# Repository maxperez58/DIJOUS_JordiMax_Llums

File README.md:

View this project on [CADLAB.io](https://cadlab.io/project/28977). 

DIJOUS_JordiMax_Llums

## Autors
- Max Pérez (@maxperez58)
- Jordi Godàs (@Jordi_Godas)

## Versió - v1.0 ## Curs - Assignatura de Disseny de PCBs amb KiCad - [Curs 2024-2025]

## Objectiu Descripció breu de l'objectiu del projecte.

L'objectiu d'aquest projecte és la realització d'un sistema de control per els diferents tipus de llums d'un vehícle automòvil. A més a més, s'ha incorporat un motor per al control de l'escombreta neteja-fars.

## Requisits i especificacions
- Llums curtes.
- Llums d'encreuament.
- Llums de circulacio dïurna.
- Intermitents.
- Motor escombreta neteja-fars.
- Sensor digital de llum, per activar les llums.

## Diagrama de blocs (Afegiu una imatge del diagrama de blocs)

_Figura 1.1: Diagrama de Blocs del nostre projecte_

## Taula de components
| Descripció | Manufacturer Number | Package | Datasheet | Proveïdor | Unitats |
|------------|--------------------|---------|----------|----------|---------|
| LDO-5V | REG1117-5 |SMD| [LT1117-5](https://www.mouser.es/datasheet/2/609/1117fd-2953685.pdf)| Mouser | 1 |
| LDO-3.3V | ADP7112ACBZ-3.3-R7 |SMD| [ADP7112ACBZ-3.3-R7 ](https://www.mouser.es/datasheet/2/609/ADP7112-3121706.pdf)| Mouser | 1 |
| Sensor de llum | BH1750FVI-TR |SMD| [BH1750FVI-TR](https://www.mouser.com/catalog/specsheets/Rohm_11162017_ROHMS34826-1.pdf)| Mouser | 1 |
| Relé | G5LE-1 DC12 |TO-220| [G5LE-1 DC12](https://www.mouser.es/datasheet/2/307/en_g5le-3447037.pdf)| Mouser | 2 |
| Buck converter | LM2596T-ADJ |SMD| [LM2596T-ADJ](https://www.ti.com/lit/ds/symlink/lm2596.pdf)| Texas Instruments | 1 |
| Transciever| MCP2551-I-SN |SMD| [MCP2551-I-SN](https://ww1.microchip.com/downloads/en/devicedoc/21667d.pdf) | Texas Instruments | 1 |
| Microcontrolador | PIC18F2580-I/SO |SMD| [PIC18F2580-I/SO](https://www.mouser.es/datasheet/2/268/39637d-3443674.pdf) | Mouser | 1 |
| Transistor NMOS | Si7336ADP |SMD| [Si7336ADP](https://www.vishay.com/docs/73152/si7336adp.pdf)| Mouser | 4 |
| Transistor BJT | ZXTN19020DFFTA |SMD| [ZXTN19020DFFTA](https://www.diodes.com/assets/Datasheets/ZXTN19020DFF.pdf) | Mouser | 5 |
| Traductor (3.3V-5V) | PCA9306D |SMD|[PCA9306D](https://www.ti.com/lit/ds/symlink/pca9306.pdf?ts=1743021004009&ref_url=https%253A%252F%252Fwww.ti.com%252Fproduct%252FPCA9306) | Mouser | 1 |
| Sensor hall | TMAG5124G1CEDBZRQ1 |SMD| [TMAG5124G1CEDBZRQ1](https://www.ti.com/lit/ds/symlink/tmag5124-q1.pdf?ts=1743694512003&ref_url=https%253A%252F%252Fwww.mouser.es%252F) | Mouser | 1 |
| OPAMP's | LT6202CS5 |SMD| [LT6202CS5](https://www.mouser.es/datasheet/2/609/620234fd-2955338.pdf) | Mouser | 1 |
| Voltage Regulator | TLV1117-33 |SMD| [TLV1117-33](http://www.ti.com/lit/ds/symlink/tlv1117.pdf) | Mouser | 1 |
| Cristall | XT9M20ANA8M |SMD| [XT9M20ANA8M](https://datasheet.octopart.com/XT9M20ANA8M-Vishay-datasheet-41303490.pdf) | Mouser | 1 |
| Inductance | Ms 42 / 47 µH |SMD| [Ms 42 / 47 µH](https://neosid.de/import-data/product-pdf/neoFestind_Ms42.pdf) | Mouser | 1 |
| Diode | 1N4002 |THT| [1N4002](https://diotec.com/request/datasheet/1n4001.pdf) | Mouser | 1 |
| Diode | 1N5817 |THT| [1N5817](http://www.vishay.com/docs/88525/1n5817.pdf) | Mouser | 4 |
| LED | APTR3216PGW |SMD| [APTR3216PGW](https://www.mouser.es/datasheet/2/216/kingbright_kngbd00006-5-1736195.pdf) | Mouser | 2 |
| Zener diode | BZX84C39 |SMD| [BZX84C39](https://diotec.com/request/datasheet/bzx84c2v4.pdf) | Mouser | 1 |
| Diode | 1N4148 |THT| [1N4148](https://assets.nexperia.com/documents/data-sheet/1N4148_1N4448.pdf) | Mouser | 1 |
| Diode Schottky | SS3P5HM3/84A |SMD| [SS3P5HM3/84A](https://www.vishay.com/docs/88944/ss3p3.pdf) | Mouser | 1 |

## Funcionalitats de les diverses seccions del nostre circuit
- [ ] Secció 1: secció de Power que converteix els 12 volts de VBAT a 5 volts per +Vcc i els 3.3 volts pel sensor.
- [ ] Secció 2: resistències pull-down a l'input per evitar una entrada descontrolada en cas de no connexió.
- [ ] Secció 3: secció del sensor amb traductor de nivell per garantir la bona comunicació entre sensor i microcontrolador.
- [ ] Secció 4: Etapa d'entrada del sensor Hall, el qual està destinat a comptar les voltes del motor.
- [ ] Secció 5: Etapa de comunicacions basada en un transciever el qual serveix per connectar el micro a un bus CAN.
- [ ] Secció 6: Etapa digital, formada pel micro i els seus I/0 + ICSP + Clock
- [ ] Secció 7: Pont-H + resistència Shunt, que controlen el sentit de gir del motor i detecten possibles pics de tensió
- [ ] Secció 8: etapa de selecció, on segons el corrent de base dels transistors i el voltatge aplicat al relé, s'escull un tipus d'iluminació o un altre.
- [ ] Secció 9: etapa reservada pels outputs i el connector DB-9 del bus CAN

## Historial de canvis 
| Data | Autor | Branch | Descripció |
|------|------|--------|------------| 
| 2025-03-17 | Max Pérez | `main` | Creació del projecte |
| 2025-03-17 | Max Pérez | `main` | LDO y output select stage |
| 2025-03-18 | Max Pérez | `main` | Conexiones básicas micro|
| 2025-03-18 | Max Pérez | `main` |Bloque transceiver, safe input y Clock|
| 2025-03-18 | Max Pérez |  `main` |Mejora estética|
| 2025-03-19 | Jordi Godàs | `main`|Acabar el diagrama de blocs 1.0|
| 2025-03-19 | Jordi Godàs |  `main` |Acabar el power point de la presentació|
| 2025-03-21 | Max Pérez | `main` |Creación esquemático 1.0|
| 2025-03-21 | Max Pérez | `main` |Bloques Clock, Communication, Digital Esquemático 1.0|
| 2025-03-21 | Max Pérez |  `main` |Bloques Input, Sensor, Power Esquemático 1.0|
| 2025-03-22 | Max Pérez |  `main` |Mejora etapa Power cambiando DC/DC + LDO por Buck|
| 2025-03-21 | Max Pérez | `main` |Capacidades desacoplo, comentar esquemático y bloque output|
| 2025-03-24 | Max Pérez |  `main` |Simulación Power stage (1 buck y 2 LDO). Exitosa|
| 2025-03-25 | Max Pérez |  `main` |Simulación Power stage (1 buck y 2 LDO) v2 y simulación Puente H|
| 2025-03-27 | Jordi Godàs |  `main` | Actualizar presentacion |
| 2025-03-27 | Jordi Godàs |  `main` | Actualizar el diagrama de bloques y el esquematico con lo dicho en clase por el profesor |
| 2025-03-29 | Max Pérez |  `main` |simulación Puente H v2|
| 2025-03-31 | Max Pérez |  `main` |Placement algunos componentes, separación planos masa y potencia. Routing Transciever, puente H y algun Input Output|
| 2025-04-02 | Jordi Godàs |  `main` | Acabar el layout de la pcb |
| 2025-04-02 | Jordi Godàs |  `main` | Actualizar presentacion |
| 2025-04-02 | Max Pérez |  `main` |GND de SMD + algun ruteo puntual. DRC sin errores|
| 2025-04-03 | Jordi Godàs |  `main` | Cambio del LDO-3.3V y placement en el esquematico |
| 2025-04-03 | Jordi Godàs |  `main` | Update readme |
| 2025-04-06 | Jordi Godàs |  `main` | Update pcb, bigger paths and better organitzation |
| 2025-04-06 | Jordi Godàs |  `main` | Update schemetatic, minor changes |
| 2025-04-07 | Jordi Godàs |  `main` | Finished layout, ERC passed |
| 2025-04-12 | Max Pérez |  `main` | Update readme: update componentes usados + diagrama bloques i funcionalidades secciones|
| 2025-04-07 | Max Pérez |  `main` | Update Esquemàtic: nombrar nodos + corrección conexión etapa Shut|
| 2025-04-09 | Jordi Godàs |  `main` | Update layout: 2CI ERC passed |
| 2025-04-12 | Max Pérez |  `main` | Cambio LDO a 5V dado a la footprint conflictiva del anterior |
| 2025-04-12 | Max Pérez |  `main` | Revisión y sustitución de footprints mal asignadas, así como reorganización en el layout de la etapa de potencia |
| 2025-04-20 | Max Pérez |  `main` | Matriu de preus per a tirada curta PCBs|
| 2025-04-20 | Max Pérez |  `main` | Generació Gerbers|
| 2025-04-20 | Max Pérez |  `main` | Búsqueda precios JCL PCB y referencias en su catálogo|
| 2025-04-23 | Jordi Godàs |  `main` | Tirada curta dels presupostos |

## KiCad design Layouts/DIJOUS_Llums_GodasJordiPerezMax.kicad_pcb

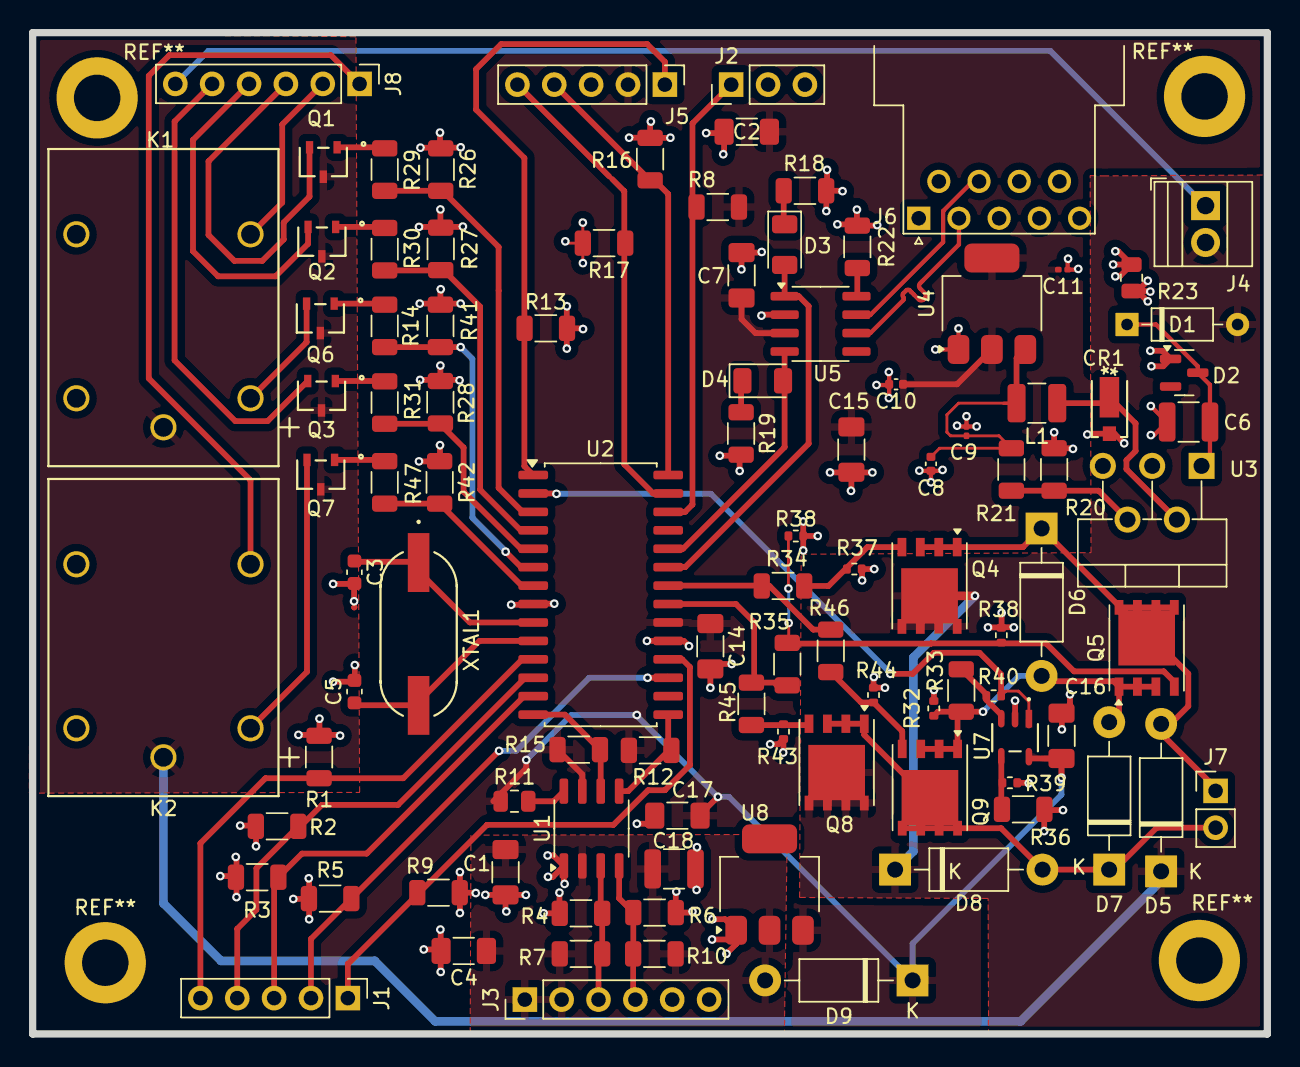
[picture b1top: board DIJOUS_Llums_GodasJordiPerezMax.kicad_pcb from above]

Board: 2 copper layers, 85.1 x 69.0 mm, 100 parts (0 on the bottom side), 61 nets.

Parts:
C1, C2, C4, C7, C14, C16, C17: 100nF; C_1206_3216Metric_Pad1.33x1.80mm_HandSolder
C3, C5: 56pF; C_0603_1608Metric
C6, C18: 100uF; C_1210_3225Metric
C8: 4.7uF; C_0402_1005Metric
C9: 10u; C_0201_0603Metric
C10: 22u; C_0402_1005Metric
C11: 10uF; C_0201_0603Metric
C15: 4.7uF; C_1206_3216Metric_Pad1.33x1.80mm_HandSolder
CR1: SS3P5HM3/84A; CR_5HM3&slash_84A_VIS
D1: 1N4148; D_DO-35_SOD27_P7.62mm_Horizontal
D2: BZX84Cxx; SOT-23
D3, D4: LED; LED_1206_3216Metric
D5, D6, D7, D8: 1N5817; D_DO-41_SOD81_P10.16mm_Horizontal
D9: 1N4002; D_DO-41_SOD81_P10.16mm_Horizontal
J1: Conn_01x05_Socket; PinHeader_1x05_P2.54mm_Vertical
J2: Conn_01x03; PinHeader_1x03_P2.54mm_Vertical
J3: Conn_01x06; PinHeader_1x06_P2.54mm_Vertical
J4: Screw_Terminal_01x02; TerminalBlock_Xinya_XY308-2.54-2P_1x02_P2.54mm_Horizontal
J5: Conn_01x05; PinHeader_1x05_P2.54mm_Vertical
J6: DE9_Plug; DSUB-9_Female_Horizontal_P2.77x2.54mm_EdgePinOffset9.40mm
J7: Conn_01x02; PinHeader_1x02_P2.54mm_Vertical
J8: Conn_01x06_Socket; PinHeader_1x06_P2.54mm_Vertical
K1, K2: G5LE-1 DC12; RELAY_G5LE-1 DC5_OMR
L1: 47uH; L_1210_3225Metric
Q1, Q2, Q3, Q6, Q7: ZXTN19020DFFTA; ZXTN19020DFFTA_DIO
Q4, Q5, Q8, Q9: Si7336ADP; PowerPAK_SO-8_Single
R1, R2, R3, R4, R5, R6, R9, R13, R16, R17, R18, R19, R33, R34, R35, R36, R45, R46: 1k; R_1206_3216Metric
R7, R10, R12, R15: 4.7k; R_1206_3216Metric
R8: 220; R_1206_3216Metric
R11: 200k; C_0805_2012Metric
R14, R26, R27, R28, R29, R30, R31, R41, R42, R47: 100; R_1206_3216Metric
R20: 2k; R_1206_3216Metric
R21: 6.81k; R_1206_3216Metric
R22: 47k; R_1206_3216Metric
R23: 0; R_0805_2012Metric
R32: 100m; R_0402_1005Metric
R37, R38, R38#2, R39, R40, R43, R44: 10k; R_0402_1005Metric
U1: PCA9306D; SO-8_3.9x4.9mm_P1.27mm
U2: PIC18F2580-I/SO; SOIC-28W_7.5x17.9mm_P1.27mm
U3: LM2596T-ADJ; TO-220-5_P3.4x3.7mm_StaggerOdd_Lead3.8mm_Vertical
U4: LT1117-5.0; SOT-223-3_TabPin2
U5: MCP2551-I-SN; SOIC-8_3.9x4.9mm_P1.27mm
U7: LT6202CS5; S_5_ADI
U8: TLV1117-33; SOT-223
XTAL1: XT9M20ANA8M; XTAL_ANA8M_VIS

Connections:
+3.3V: C1.2, C4.1, C18.1, D9.2 (A), J3.1, J3.2, R7.2, R10.2, U1.2 (VREF1), U8.2 (VO)
+5V: C2.1, C7.1, C10.1, C11.1, C14.1, C15.1, C16.1, C17.2, D9.1 (K), J5.2, R8.1, R11.1, R12.2, R15.2, U1.7 (VREF2), U2.20 (VDD), U4.2 (VO), U5.3 (VDD), U7.5 (V+), U8.3 (VI)
+12V: D1.2 (A), D5.1 (K), D8.1 (K), J4.2, K1.1, K2.1, Q1.3, Q2.3, Q3.3, Q4.5 (D), Q6.3, Q7.3, Q8.5 (D)
/BJTbase1: Q1.1, R29.2
/BJTbase2: Q2.1, R30.2
/BJTbase3: Q3.1, R31.2
/BJTbase4: Q6.1, R14.2
/BJTbase5: Q7.1, R47.2
/BJTemissor4: K1.2, Q6.2
/BJTemissor5: K2.2, Q7.2
/Buck_FB: R20.1, R21.1, U3.4 (FB)
/Buck_IN: C6.1, D1.1 (K), D2.3 (K), U3.1 (VIN)
/Buck_OUT: CR1.1, L1.1, U3.2 (OUT)
/ENABLE: R11.2, U1.8 (EN)
/LDO5V_IN: C8.1, C9.1, L1.2, R21.2, U4.3 (VI)
/LEDRX: D4.1 (K), R19.1
/LEDTX: D3.1 (K), R18.1
/NMOSbase11: Q4.4 (G), R34.2, R37.1
/NMOSbase12: Q8.4 (G), R43.1, R45.1
/NMOSbase21: Q5.4 (G), R35.2, R38.1, R38#2.1
/NMOSbase22: Q9.4 (G), R44.1, R46.1
/OSC1: C3.1, U2.9 (OSC1/CLKI/RA7), XTAL1.1
/OSC2: C5.1, U2.10 (OSC2/CLKO/RA6), XTAL1.2
/SHUT_OPV+: R33.2, R40.2, U7.3 (+IN)
/SHUT_OPV-: R36.2, R39.2, U7.4 (-IN)
/TRANS_Rs: R22.1, U5.8 (Rs)
Blinkers: J8.3, Q1.2
Brushless: J8.5, Q3.2
CANH_O: J6.7, U5.7 (CANH)
CANL_O: J6.2, U5.6 (CANL)
CANRX: D4.2 (A), U2.24 (RB3/CANRX), U5.4 (RXD)
CANTX: D3.2 (A), U2.23 (RB2/INT2/CANTX), U5.1 (TXD)
Daytime lights: J8.4, Q2.2
GND: C1.1, C2.2, C3.2, C4.2, C5.2, C7.2, C10.2, C11.2, C14.2, C15.2, C16.2, C17.1, C18.2, J2.2, J2.3, J3.5, J3.6, J5.3, J6.5, R1.2, R2.2, R3.2, R4.2, R5.2, R6.2, R9.2, R13.2, R16.2, R17.2, R18.2, R19.2, R22.2, R23.1, R26.2, R27.2, R28.2, R32.2, R36.1, R37.2, R38.2, R38#2.2, R39.1, R41.2, R42.2, R43.2, R44.2, U1.1 (GND), U2.8 (VSS), U2.19 (VSS), U4.1 (GND), U5.2 (VSS), U7.2 (V-), U8.1 (GND)
GNDPWR: C6.2, C8.2, C9.2, CR1.2, D2.1 (A), J4.1, J8.6, K1.4, K1.5, K2.4, K2.5, R20.2, R23.2, U3.3 (GND), U3.5 (~ON/OFF)
High Beam: J8.2, K1.3
Low Beam: J8.1, K2.3
MCLR: J5.1, R13.1, U2.1 (*MCLR/VPP/RE3)
Motor_in1: R34.1, R46.2, U2.22 (RB1/INT1/AN8)
Motor_in2: R35.1, R45.2, U2.21 (RB0/INT0/AN10)
Motor_o1: D5.2 (A), D6.1 (K), J7.1, Q4.1 (S), Q4.2 (S), Q4.3 (S), Q5.5 (D)
Motor_o2: D7.1 (K), D8.2 (A), J7.2, Q8.1 (S), Q8.2 (S), Q8.3 (S), Q9.5 (D)
PGC: J5.5, R17.1, U2.27 (RB6/KBI2/PGC)
PGD: J5.4, R16.1, U2.28 (RB7/KBI3/PGD)
RA1: R26.1, R29.1, U2.3 (RA1/AN1)
RA2: R27.1, R30.1, U2.4 (RA2/AN2/VREF-)
RA3: R28.1, R31.1, U2.5 (RA3/AN3/VREF+)
RA4: R14.1, R41.1, U2.6 (RA4/T0CKI)
RA5: R42.1, R47.1, U2.7 (RA5/AN4/*SS/HLVDIN)
RB5: J2.1, R8.2, U2.26 (RB5/KBI1/PGM)
RC0: J1.5, R1.1, U2.11 (RC0/T1OSO/T13CKI)
RC1: J1.4, R2.1, U2.12 (RC1/T1OSI)
RC2: J1.3, R3.1, U2.13 (RC2/CCP1)
RC6: J1.2, R5.1, U2.17 (RC6/TX/CK)
RC7: J1.1, R9.1, U2.18 (RC7/RX/DT)
SCL_O: R15.1, U1.6 (SCL2), U2.14 (RC3/SCK/SCL)
SCl: J3.3, R4.1, R7.1, U1.3 (SCL1)
SDA: J3.4, R6.1, R10.1, U1.4 (SDA1)
SDA_O: R12.1, U1.5 (SDA2), U2.15 (RC4/SDI/SDA)
SHUT_OUT: R40.1, U2.2 (RA0/AN0), U7.1 (OUT)
Shutin: D6.2 (A), D7.2 (A), Q5.1 (S), Q5.2 (S), Q5.3 (S), Q9.1 (S), Q9.2 (S), Q9.3 (S), R32.1, R33.1

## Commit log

2025-03-17 Creació README
    Basic info to README
2025-03-17 Diagrama de Bloques 1a etapa
    Añadido las salidas, un relé para control de luces, 3 transistores que serán controlados por el micro y 3 reguladores de tensión para el motor y las distintas luces
2025-03-17 README actualitzat a 17/03/2025
2025-03-17 README actualizado
2025-03-18 DiagramaBloquesV1.1
    Se ha añadido el micro, transciever, clock y bloque seguridad input. Respecto a la versión anterior, se ha reorganizado para una mejor comprensión del diseño
2025-03-19 Versió final del diagrama de blocs
2025-03-19 Bloques esenciales
    Cadena de bloques esencial. Cada uno contiene sub-bloques, los cuales están incluidos en el diagrama de bloques subido por Jordi
2025-03-21 Esquemático del proyecto
    Primer esbozo. Se ha añadido el microcontrolador con algunas de las entradas (botonera, clock , i2c, busCAN y +Vcc), y los módulos de sensor, input e input safe (díodos de protección...), power stage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
2025-03-21 Backlink to CADLAB.io has been added.
2025-03-21 Componentes esquemáticos
2025-03-21 prueba
2025-03-21 new2
2025-03-22 pruebaa
2025-03-22 Esquem
2025-03-22 Esquemático y pcb
2025-03-22 diagrama_de_bloques_v.4
2025-03-23 3rd revision of the schematic
2025-03-23 components utilitzats en el disseny
2025-03-24 LTSpice Power Stage
    Etapa de Power simulada. Si no hay problemas con el CAD de estos modelos, es definitiva. Consta de un Buck y 2 LDO
2025-03-24 schematic ver4
2025-03-25 LM2596 spice model
2025-03-25 Carpeta para guardar Datasheets
2025-03-25 Update DIJOUS_Llums_GodasJordiPerezMax
    Update v4 by Jordi
2025-03-25 CAD models
    Biblioteca para añadir modelos CAD. Incluye el Buck LM2596
2025-03-25 Create Schematics
2025-03-25 Rename Schematics to Schematics\
2025-03-25 Update and rename Schematics\ to Schematics/P
2025-03-25 Create d
2025-03-25 Rename DIJOUS_Llums_GodasJordiPerezMax.kicad_pcb to Layouts/DIJOUS_Llums_GodasJordiPerezMax.kicad_pcb
2025-03-25 Rename DIJOUS_Llums_GodasJordiPerezMax.kicad_pro to .pro/DIJOUS_Llums_GodasJordiPerezMax.kicad_pro
2025-03-25 Rename Diagrama_de_bloques.svg to Diagrama Bloques/Diagrama_de_bloques.svg
2025-03-25 Update and rename PIC18F258-I_SP.kicad_sym to CAD models/PIC18F258-I_SP.kicad_sym
    CAD model for PIC18F258
2025-03-25 Update and rename RP-1206S.kicad_sym to CAD models/RP-1206S.kicad_sym
    RP-1206s CAD model
2025-03-25 Rename DIJOUS_Llums_GodasJordiPerezMax_v4/DIJOUS_Llums_GodasJordiPerezMax.kicad_pcb to DIJOUS_Llums_GodasJordiPerezMax_v4/Layouts/DIJOUS_Llums_GodasJordiPerezMax.kicad_pcb
    Layout
2025-03-25 Rename DIJOUS_Llums_GodasJordiPerezMax_v3/DIJOUS_Llums_GodasJordiPerezMax.kicad_pcb to DIJOUS_Llums_GodasJordiPerezMax_v3/Layouts/DIJOUS_Llums_GodasJordiPerezMax.kicad_pcb
    Layout
2025-03-25 Rename DIJOUS_Llums_GodasJordiPerezMax_v4/DIJOUS_Llums_GodasJordiPerezMax.kicad_pro to DIJOUS_Llums_GodasJordiPerezMax_v4/.pro/DIJOUS_Llums_GodasJordiPerezMax.kicad_pro
    .pro
2025-03-25 Rename DIJOUS_Llums_GodasJordiPerezMax_v3/Layouts/DIJOUS_Llums_GodasJordiPerezMax.kicad_pcb to Layouts/DIJOUS_Llums_GodasJordiPerezMax_v3DIJOUS_Llums_GodasJordiPerezMax.kicad_pcb
    Layout
2025-03-25 PIC18F2580 datasheet
    PIC18F2580 datasheet
2025-03-25 Rename DIJOUS_Llums_GodasJordiPerezMax.kicad_pro to DIJOUS_Llums_GodasJordiPerezMax_v3DIJOUS_Llums_GodasJordiPerezMax.kicad_pro
    .pro
2025-03-25 Update and rename DIJOUS_Llums_GodasJordiPerezMax_v3/Schematics/DIJOUS_Llums_GodasJordiPerezMax.kicad_sch to Schematics/DIJOUS_Llums_GodasJordiPerezMax_v3DIJOUS_Llums_GodasJordiPerezMax.kicad_sch
    Esquemático
2025-03-25 Rename DIJOUS_Llums_GodasJordiPerezMax_v4/.pro/DIJOUS_Llums_GodasJordiPerezMax.kicad_pro to .pro/DIJOUS_Llums_GodasJordiPerezMax_v4DIJOUS_Llums_GodasJordiPerezMax.kicad_pro
    .pro
2025-03-25 Rename DIJOUS_Llums_GodasJordiPerezMax_v4/Layouts/DIJOUS_Llums_GodasJordiPerezMax.kicad_pcb to Layouts/DIJOUS_Llums_GodasJordiPerezMax_v4DIJOUS_Llums_GodasJordiPerezMax.kicad_pcb
    Layouts
2025-03-25 Update and rename DIJOUS_Llums_GodasJordiPerezMax_v4/Schematics/DIJOUS_Llums_GodasJordiPerezMax.kicad_sch to Schematics/DIJOUS_Llums_GodasJordiPerezMax_v4DIJOUS_Llums_GodasJordiPerezMax.kicad_sch
    Esquemático
2025-03-25 Fusible
    Fusible para proteger de picos de corriente (3A)
2025-03-25 Input and Power stage simulation
    Simulación de etapa Input y Power. Consta de la etapa Safe Input (díodos protección) + Buck converter y 2 LDO. Funciona correctamente
2025-03-25 H bridge
    Puente H para controlar el sentido de giro del motor. El ingeniero de software también implementará un código que tenga calculado el fin de carrera.
2025-03-25 Rename ltspice/h_bridge.asc to ltspice/H-bridge/h_bridge.asc
2025-03-25 Update h_bridge.asc
    2nd version of h_bridge
2025-03-25 schematic v5
2025-03-26 shcematic v6- versio per presentar
2025-03-26 diagrama de bloques v2
    revisión después de hacer el esquemático
2025-03-26 Create Prova
2025-03-26 presentació per l'esquematic
2025-03-26 Presentació per l'esquemàtic
2025-03-27 PCA9306 datasheet
2025-03-27 update DIJOUS_Llums_GodasJordiPerezMax.kicad_sch
    versió per presentar l'esquemàtic-definitiva
2025-03-27 Update DIJOUS_Llums_GodasJordiPerezMax.kicad_sch
    versió pre presentar l'esquemàtic- definitiva
2025-03-27 Update GodasJordiPerezMax_PresentacióEDDLlums.pdf
    versió per presentar l'esquemàtic-definitiva
2025-03-27 Update DIJOUS_Llums_GodasJordiPerezMax.kicad_pro
    update after class
2025-03-29 Update DIJOUS_Llums_GodasJordiPerezMax.kicad_sch
    Resistencias botones y update puente + shunt y alguna footprint
2025-03-29 Update DIJOUS_Llums_GodasJordiPerezMax.kicad_sch
    Nueva actualización Puente H+ resistencia Shunt. Se han añadido bastantes huellas. Falta huellas restantes y la etapa Output select y se puede empezar Placement
2025-03-29 Update H_bridge
    Versión mejorada puente H. Definitiva?
2025-03-30 Update DIJOUS_Llums_GodasJordiPerezMax.kicad_sch
    Alguna pequeña corrección del esquemático. He añadido un par de huellas y cambiado algún pin que estaba mal. Faltan aún huellas por poner y alguna etapa por revisar (la del Hall y el Output select st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
2025-03-30 Update DIJOUS_Llums_GodasJordiPerezMax.kicad_pcb
    Primer Placement del proyecto. He hecho placement de los inputs, el buck converter y su etapa de filtrado, el puente H, el DB-9, la etapa de comunicaciones y del intranivel. Faltan algunas footprints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
2025-03-30 Update
    DIJOUS_Llums_GodasJordiPerezMax.kicad_pro
2025-03-30 opmap
2025-03-30 Rename ul_G5LE-1-DC12.zip to Schematics/ul_G5LE-1-DC12.zip
2025-03-30 Rename ul_G5LE-1-DC12.zip to ul_G5LE-1-DC12.zip
2025-03-30 Rename ul_PIC18F2580-I-SO.zip to components/ul_PIC18F2580-I-SO.zip
2025-03-30 Rename ul_SS3P5HM3-84A.zip to components/ul_SS3P5HM3-84A.zip
2025-03-30 Rename ul_XT9M20ANA8M.zip to components/ul_XT9M20ANA8M.zip
2025-03-30 Rename ul_ZXTP19020DFFTA.zip to components/ul_ZXTP19020DFFTA.zip
2025-03-31 Update DIJOUS_Llums_GodasJordiPerezMax.kicad_sch
    Se ha cambiado alguna etiqueta
2025-03-31 Update DIJOUS_Llums_GodasJordiPerezMax.kicad_pcb
    Primer avance en PCB. Se ha hecho Placement de una parte de los componentes, separación de planos de masa y potencia y el routing del Buck, del puente H, algunas conexiones del micro e inputs y outpu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
2025-04-02 Update esquemático
    Versión 2.0 del esquemático. Cambios notables respecto a la semana pasada
2025-04-02 Update Layout
    Versión 1.0 del Layout. En este Commit, se han ruteado algunos GND de SMD y mejorado la interconexión en algunos puntos concretos. A falta del okey del otro compañero
2025-04-02 diagrama de bloques v2
2025-04-02 Update Layout
2025-04-03 Update esquemático
2025-04-07 Update Schematic
2025-04-08 Update diagrama de bloques
    Cambio formato
2025-04-12 Update etapa Power
    Cambio en el LDO que convierte a 5V por footprint conflictiva
2025-04-12 Update esquemàtic
    S'ha modificat el LDO de 6 a 5V i alguns footprints que no estaven ben assignats
2025-04-12 Update PCB
    S'ha reorganitzat la zona de potència gràcies a un forat que ha deixat el DB-9. S'han col·locat les noves footprints canviades
2025-04-20 Cambio footprint bobina
2025-04-20 Ruteado footprint bobina
2025-04-20 Matriu preus (format pdf)
2025-04-20 Rename Precios para EDD - GodasJordi_PerezMax - Hoja 1.pdf to MatriuPreus/Precios para EDD - GodasJordi_PerezMax - Hoja 1.pdf
